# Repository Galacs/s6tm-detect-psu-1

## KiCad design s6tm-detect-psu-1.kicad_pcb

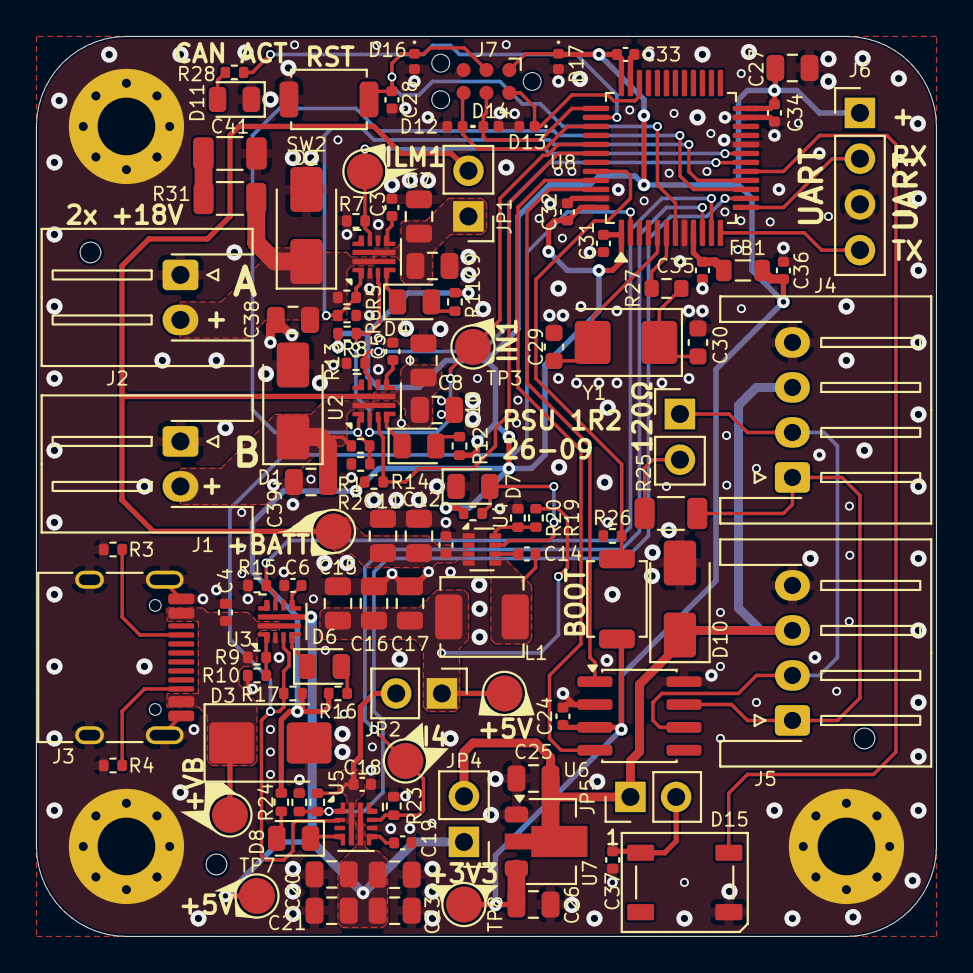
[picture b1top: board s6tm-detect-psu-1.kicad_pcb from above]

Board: 4 copper layers, 50.0 x 50.0 mm, 122 parts (0 on the bottom side), 57 nets.

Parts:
C3, C5, C6, C19: 1n; C_0402_1005Metric
C4, C18, C35, C36, C37: 1u; C_0402_1005Metric
C7, C8, C9, C10, C11, C12, C15, C16, C17, C20, C21, C22, C23, C25, C26, C27, C38, C39: 10u; C_0805_2012Metric
C13, C14, C24, C28, C31, C32, C33, C34: 0u1; C_0402_1005Metric
C29, C30: 20p; C_0603_1608Metric
C41: 2u2; C_1206_3216Metric
D1, D2, D10: SMAJ22CA; D_SMA
D3: SMBJ6.0CA; D_SMB
D4, D5, D6, D8: GREEN; LED_0805_2012Metric
D7: RED; LED_0805_2012Metric
D11: YELLOW; LED_0805_2012Metric
D12, D13, D14, D16, D17: H5VU10U; Diode_DFN1006
D15: WS2812B; LED_WS2812B_PLCC4_5.0x5.0mm_P3.2mm
FB1: 600Ω@100M; L_0805_2012Metric
H1, H2, H3: MountingHole; ToolingHole_1.152mm
H6, H7, H8: MountingHole_Pad; MountingHole_3.2mm_M3_Pad_Via
J1, J2: Conn_01x02; JST_XH_S2B-XH-A-1_1x02_P2.50mm_Horizontal
J3: USB_C_Receptacle_USB2.0_14P; USB_C_Receptacle_HRO_TYPE-C-31-M-12
J4, J5: Conn_01x04; JST_XH_S4B-XH-A-1_1x04_P2.50mm_Horizontal
J6: Conn_01x04_Pin; PinHeader_1x04_P2.54mm_Vertical
J7: TC2030; Tag-Connect_TC2030-IDC-NL_2x03_P1.27mm_Vertical
JP1, JP2, JP3, JP4, JP5: Jumper_2_Small_Bridged; PinHeader_1x02_P2.54mm_Vertical
L1: 3u3; L_Sunlord_MWSA0402S
R1, R5, R9, R13, R14, R17, R20, R21, R26: 10k; R_0402_1005Metric
R2, R6, R15, R23: 1k; R_0402_1005Metric
R3, R4, R11, R12, R16, R18, R24, R28: 5k1; R_0402_1005Metric
R7, R8, R10, R22: 3k3; R_0402_1005Metric
R19: 52k3; R_0402_1005Metric
R25: 120; R_1206_3216Metric
R27: 560; R_0603_1608Metric
R31: 1; R_1206_3216Metric
SW1, SW2: SW_Push; SW_SPST_TS-1088-xR020
TP1, TP2, TP3, TP4, TP5, TP6, TP7, TP8: TestPoint; TestPoint_Pad_D2.0mm
U1, U2, U3, U5: TPS259470x; Texas_RPW0010A_VQFN-HR-10_2x2mm_P0.5mm
U4: TPS62933; SOT-583-8
U6: SN65HVD230; SOIC-8_3.9x4.9mm_P1.27mm
U7: HT753-1; SOT-89-3
U8: STM32F103C8Tx; LQFP-48_7x7mm_P0.5mm
Y1: 8M; Crystal_SMD_5032-2Pin_5.0x3.2mm

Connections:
5_V: R21.1, R22.2, U5.1 (EN/UVLO), U8.14 (ADC1_IN4)
+3V3: C24.1, C26.1, C27.1, C31.1, C32.1, C33.1, C34.1, C36.1, D17.1 (K), FB1.2, J6.1, J7.1 (VCC), R11.2, R12.2, R13.1, R14.1, R16.2, R17.1, R18.1, R24.2, SW1.1, TP8.1 (1_1), U6.3 (VCC), U7.3 (VOUT), U8.1 (VBAT), U8.24 (VDD), U8.36 (VDD), U8.48 (VDD)
+5V: C20.1, C21.1, C22.1, C23.1, C25.1, C37.2, D10.1 (A1), D15.1 (VDD), J4.3, J5.3, JP4.1 (A), JP4.2 (B), JP5.1 (A), JP5.2 (B), TP7.1 (1_1), U3.6 (OUT), U5.6 (OUT), U7.2 (VIN)
+5V_SMPS: C15.1, C16.1, C17.1, C18.2, JP2.1 (A), JP2.2 (B), L1.2, R19.2, R21.2, TP5.1 (1_1), U5.5 (IN)
+BATT: C7.1, C8.1, C9.1, C10.1, C11.1, C12.1, C13.1, JP1.1 (A), JP1.2 (B), TP4.1 (1_1), U1.6 (OUT), U2.6 (OUT), U4.3 (VIN)
+Vbus: C4.2, D3.1 (A1), J3.A4 (VBUS), J3.A9 (VBUS), J3.B4 (VBUS), J3.B9 (VBUS), R9.2, TP1.1 (1_1), U3.5 (IN)
/Logic/BOOT: R26.2, SW1.2, U8.44 (BOOT0)
/Logic/CANH: J4.1, J5.1, R25.1, U6.7 (CANH)
/Logic/CANL: J4.2, J5.2, JP3.1 (A), U6.6 (CANL)
/Logic/CAN_RX: U6.4 (R), U8.45 (CAN_RX)
/Logic/CAN_TX: U6.1 (D), U8.46 (CAN_TX)
/Logic/NRST: C28.1, D16.1 (K), J7.3 (~RESET), SW2.2, U8.7 (NRST)
/Logic/RGB: D15.4 (DIN), U8.17 (PA7)
/Logic/SWCLK: D14.1 (K), J7.4 (SWCLK), U8.37 (SWCLK)
/Logic/SWDIO: D13.1 (K), J7.2 (SWDIO), U8.34 (SWDIO)
/Logic/SWO: D12.1 (K), J7.6 (SWO), U8.39 (PB3)
/Logic/U0RXD: J6.2, U8.13 (USART2_RX)
/Logic/U0TXD: J6.4, U8.12 (USART2_TX)
/Logic/XTAL_I: C29.1, U8.5 (RCC_OSC_IN), Y1.2
/Logic/XTAL_O: R27.2, U8.6 (RCC_OSC_OUT)
/Logic/XTAL_RO: C30.1, R27.1, Y1.1
BATT1_V: R5.1, R6.2, U1.1 (EN/UVLO), U8.16 (ADC1_IN6)
BATT2_V: R1.1, R2.2, U2.1 (EN/UVLO), U8.15 (ADC1_IN5)
GND: C3.2, C4.1, C5.2, C6.2, C7.2, C8.2, C9.2, C10.2, C11.2, C12.2, C13.2, C15.2, C16.2, C17.2, C18.1, C19.2, C20.2, C21.2, C22.2, C23.2, C24.2, C25.2, C26.2, C27.2, C28.2, C29.2, C30.2, C31.2, C32.2, C33.2, C34.2, C35.2, C36.2, C37.1, C38.2, C39.2, C41.2, D1.2 (A2), D2.2 (A2), D3.2 (A2), D7.1 (K), D10.2 (A2), D11.1 (K), D12.2 (A), D13.2 (A), D14.2 (A), D15.3 (VSS), D16.2 (A), D17.2 (A), H6.1 (1_1), H7.1 (1_1), H8.1 (1_1), J1.1, J2.1, J3.A1 (GND), J3.A12 (GND), J3.B1 (GND), J3.B12 (GND), J3.SH (SHIELD), J4.4, J5.4, J6.3, J7.5 (GND), R2.1, R3.1, R4.1, R6.1, R7.2, R8.2, R10.1, R15.2, R20.1, R22.1, R23.2, R26.1, SW2.1, U1.2 (OVLO), U1.8 (GND), U2.8 (GND), U3.2 (OVLO), U3.8 (GND), U4.1 (RT), U4.4 (GND), U5.8 (GND), U6.2 (GND), U6.8 (Rs), U7.1 (GND), U8.8 (VSSA), U8.20 (PB2), U8.23 (VSS), U8.35 (VSS), U8.47 (VSS)
ILM1: R7.1, TP2.1 (1_1), U1.9 (ILM), U8.19 (ADC1_IN9)
ILM2: R8.1, U2.9 (ILM), U8.18 (ADC1_IN8)
ILM3: R15.1, U3.9 (ILM), U8.11 (ADC1_IN1)
ILM4: R23.1, TP6.1 (1_1), U5.9 (ILM), U8.10 (ADC1_IN0)
IN1: R13.2, TP3.1 (1_1), U1.3 (AUXOFF), U2.2 (OVLO), U8.41 (PB5)
IN2: R14.2, U2.3 (AUXOFF), U8.42 (PB6)
IN3: R17.2, U3.3 (AUXOFF), U5.2 (OVLO), U8.2 (PC13)
unnamed: C41.1, R31.1
unnamed: C39.1, D1.1 (A1), J1.2, R1.2, U2.5 (IN)
unnamed: C38.1, D2.1 (A1), J2.2, R5.2, R31.2, U1.5 (IN)
unnamed: D4.2 (A), R11.1
unnamed: D4.1 (K), U1.4 (~FLT)
unnamed: D5.2 (A), R12.1
unnamed: D5.1 (K), U2.4 (~FLT)
unnamed: D6.2 (A), R16.1
unnamed: D6.1 (K), U3.4 (~FLT)
unnamed: D7.2 (A), R18.2, U4.7 (PG)
unnamed: D8.2 (A), R24.1
unnamed: D8.1 (K), U5.4 (~FLT)
unnamed: D11.2 (A), R28.2
unnamed: J3.A5 (CC1), R3.2
unnamed: J3.B5 (CC2), R4.2
unnamed: JP3.2 (B), R25.2
unnamed: C3.1, U1.7 (DVDT)
unnamed: C5.1, U2.7 (DVDT)
unnamed: C6.1, U3.7 (DVDT)
unnamed: R9.1, R10.2, U3.1 (EN/UVLO)
unnamed: C14.2, U4.6 (BST)
unnamed: R19.1, R20.2, U4.8 (FB)
unnamed: C14.1, L1.1, U4.5 (SW)
unnamed: C19.1, U5.7 (DVDT)
unnamed: R28.1, U8.38 (PA15)
unnamed: C35.1, FB1.1, U8.9 (VDDA)

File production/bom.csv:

Designator,Footprint,Quantity,Value,LCSC Part #
"C1, C18, C2, C35, C36, C37, C4",0402,7,1u,C52923
"C10, C11, C12, C15, C16, C17, C20, C21, C22, C23, C25, C26, C27, C7, C8, C9",0805,16,10u,C440198
"C13, C14, C24, C28, C31, C32, C33, C34",0402,8,0u1,C307331
"C19, C3, C5, C6",0402,4,1n,C1523
"C29, C30",0603,2,20p,C1648
"D1, D10, D2",D_SMA,3,SMBJ6.0CA,C19077544
D11,0805,1,YELLOW,C2296
"D12, D13, D14, D16, D17",Diode_DFN1006,5,H5VU10U,C22395519
D15,LED_WS2812B_PLCC4_5.0x5.0mm_P3.2mm,1,WS2812B,C2874885
D3,D_SMB,1,SMBJ6.0CA,C2925451
"D4, D5, D6, D8",0805,4,GREEN,C2297
D7,0805,1,RED,NCD0805R1
FB1,0805,1,600Ω@100M,C81034
"J1, J2",JST_XH_S2B-XH-A-1_1x02_P2.50mm_Horizontal,2,Conn_01x02,C163035
J3,USB_C_Receptacle_HRO_TYPE-C-31-M-12,1,USB_C_Receptacle_USB2.0_14P,C393939
"J4, J5",JST_XH_S4B-XH-A-1_1x04_P2.50mm_Horizontal,2,Conn_01x04,C163037
L1,L_Sunlord_MWSA0402S,1,3u3,C167207
"R1, R13, R14, R17, R20, R21, R26, R5, R9",0402,9,10k,C25744
"R10, R22, R7, R8",0402,4,3k3,C25890
"R11, R12, R16, R18, R24, R28, R3, R4",0402,8,5k1,C25905
"R15, R2, R23, R6",0402,4,1k,C11702
R19,0402,1,52k3,C2998086
R25,1206,1,120,C17909
R27,0603,1,560,C23204
"SW1, SW2",SW_SPST_TS-1088-xR020,2,SW_Push,C720477
"U1, U2, U3, U5",Texas_RPW0010A_VQFN-HR-10_2x2mm_P0.5mm,4,TPS259470x,C3662799
U4,SOT-583-8,1,TPS62933,C5219254
U6,SOIC-8_3.9x4.9mm_P1.27mm,1,SN65HVD230,C12084
U7,SOT-89-3,1,HT753-1,C14289
U8,LQFP-48_7x7mm_P0.5mm,1,STM32F103C8Tx,C8734
Y1,Crystal_SMD_5032-2Pin_5.0x3.2mm,1,8M,C115962
